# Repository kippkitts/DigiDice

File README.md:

DigiDice
========

DigiDice is a random number generator that simulates a 4, 6, 8, 10, 12, and 20 sided die.  There are six buttons, each corresponding to one of these dice, and pressing one of these buttons will generate a true random number within the selected die's range.  That number is then shown on a 2 digit 7 segment display.

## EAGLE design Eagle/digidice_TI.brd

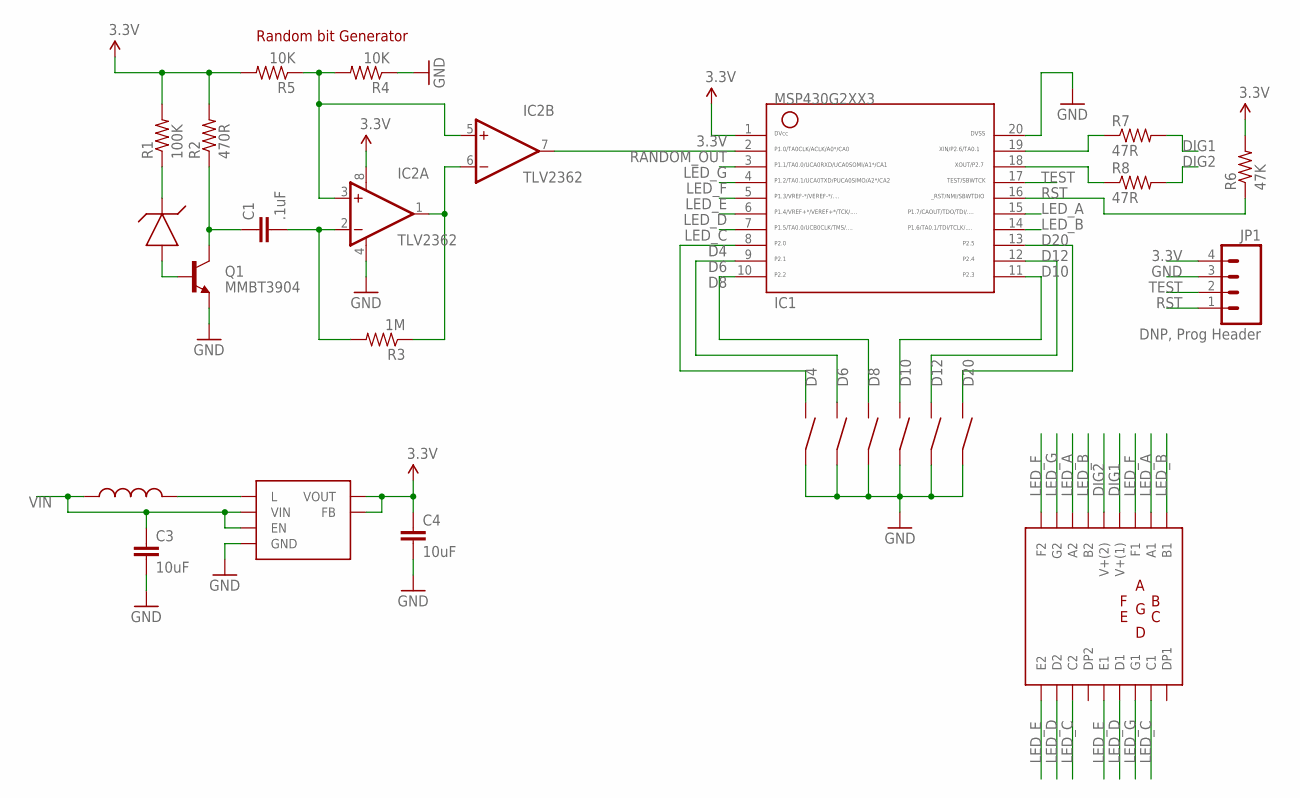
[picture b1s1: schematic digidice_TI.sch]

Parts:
C1: .1uF; 0402-CAP
C3, C4: 10uF; 0603-CAP
IC1: MSP430G2203IPW20; PW20
IC2: TLV2362; MSOP08; MPN OPA2340EA/250
IC3: TLV61225; SOT-363
JP1: DNP, Prog Header; 1X04-1.27MM
L1: PFL2015-472ML; COILCRAFT-PFL2015
Q1: MMBT3904; SOT23
R1: 100K; 0402-RES
R2: 470R; 0402-RES
R3: 1M; 0402-RES
R4, R5: 10K; 0402-RES
R6: 47K; 0402-RES
R7, R8: 47R; 0805
SW1, SW2, SW3, SW4, SW5, SW6: SPST_SWITCH; EG2513-ND
U$1: ZXRE1004FFTA; SOT23
U$2: 2DIGIT_7SEGMENT; HDSP-521E

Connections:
3.3V: C4.1, IC1.1, IC2.8 (V+), IC3.P$2 (FB), IC3.P$4 (VOUT), JP1.4, R1.2, R2.2, R5.2, R6.2
D4: IC1.8, SW6.P$2 (2)
D6: IC1.9, SW5.P$2 (2)
D8: IC1.10, SW4.P$2 (2)
D10: IC1.11, SW3.P$2 (2)
D12: IC1.12, SW2.P$2 (2)
D20: IC1.13, SW1.P$2 (2)
DIG1: R7.2, U$2.P$13 (V+(1))
DIG2: R8.2, U$2.P$14 (V+(2))
GND: C3.2, C4.2, IC1.20, IC2.4 (V-), IC3.P$3 (GND), JP1.3, Q1.2 (E), R4.1, SW1.P$1 (1), SW2.P$1 (1), SW3.P$1 (1), SW4.P$1 (1), SW5.P$1 (1), SW6.P$1 (1)
LED_A: IC1.15, U$2.P$11 (A1), U$2.P$16 (A2)
LED_B: IC1.14, U$2.P$10 (B1), U$2.P$15 (B2)
LED_C: IC1.7, U$2.P$3 (C2), U$2.P$8 (C1)
LED_D: IC1.6, U$2.P$2 (D2), U$2.P$6 (D1)
LED_E: IC1.5, U$2.P$1 (E2), U$2.P$5 (E1)
LED_F: IC1.4, U$2.P$12 (F1), U$2.P$18 (F2)
LED_G: IC1.3, U$2.P$7 (G1), U$2.P$17 (G2)
unnamed: Q1.1 (B), U$1.2 (A)
unnamed: C1.1, Q1.3 (C), R2.1
unnamed: R1.1, U$1.1 (K)
unnamed: C1.2, IC2.2 (-IN), R3.2
unnamed: IC2.1 (OUT), IC2.6 (-IN), R3.1
unnamed: IC2.3 (+IN), IC2.5 (+IN), R4.2, R5.1
unnamed: IC1.19, R7.1
unnamed: IC1.18, R8.1
unnamed: IC3.P$5 (L), L1.P$2 (2)
RANDOM_OUT: IC1.2, IC2.7 (OUT)
RST: IC1.16, JP1.1, R6.1
TEST: IC1.17, JP1.2
VIN: C3.1, IC3.P$1 (VIN), IC3.P$6 (EN), L1.P$1 (1)

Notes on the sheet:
Random bit Generator

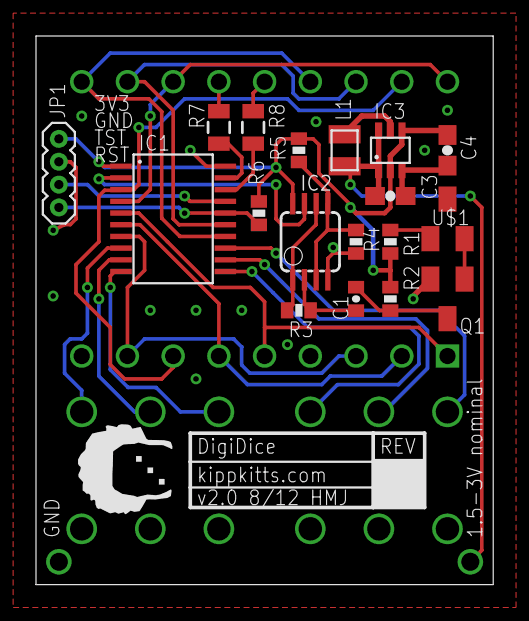
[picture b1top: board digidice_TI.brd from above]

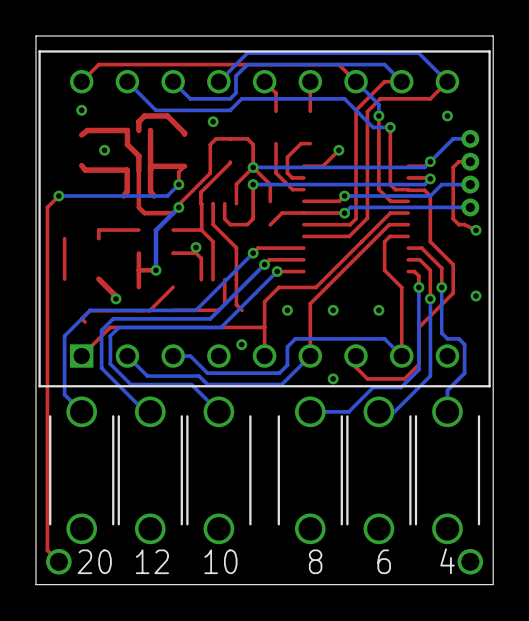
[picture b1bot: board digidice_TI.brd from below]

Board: 2 copper layers, 25.4 x 30.5 mm, 26 parts (7 on the bottom side), 30 nets.

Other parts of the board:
U$3: TOP_DOCU_5MM

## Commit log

2014-03-13 Add Eagle files

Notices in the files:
parts and their libraries:
SparkFun: Licensing: CC v3.0 Share-Alike You are welcome to use this library for commercial purposes.
